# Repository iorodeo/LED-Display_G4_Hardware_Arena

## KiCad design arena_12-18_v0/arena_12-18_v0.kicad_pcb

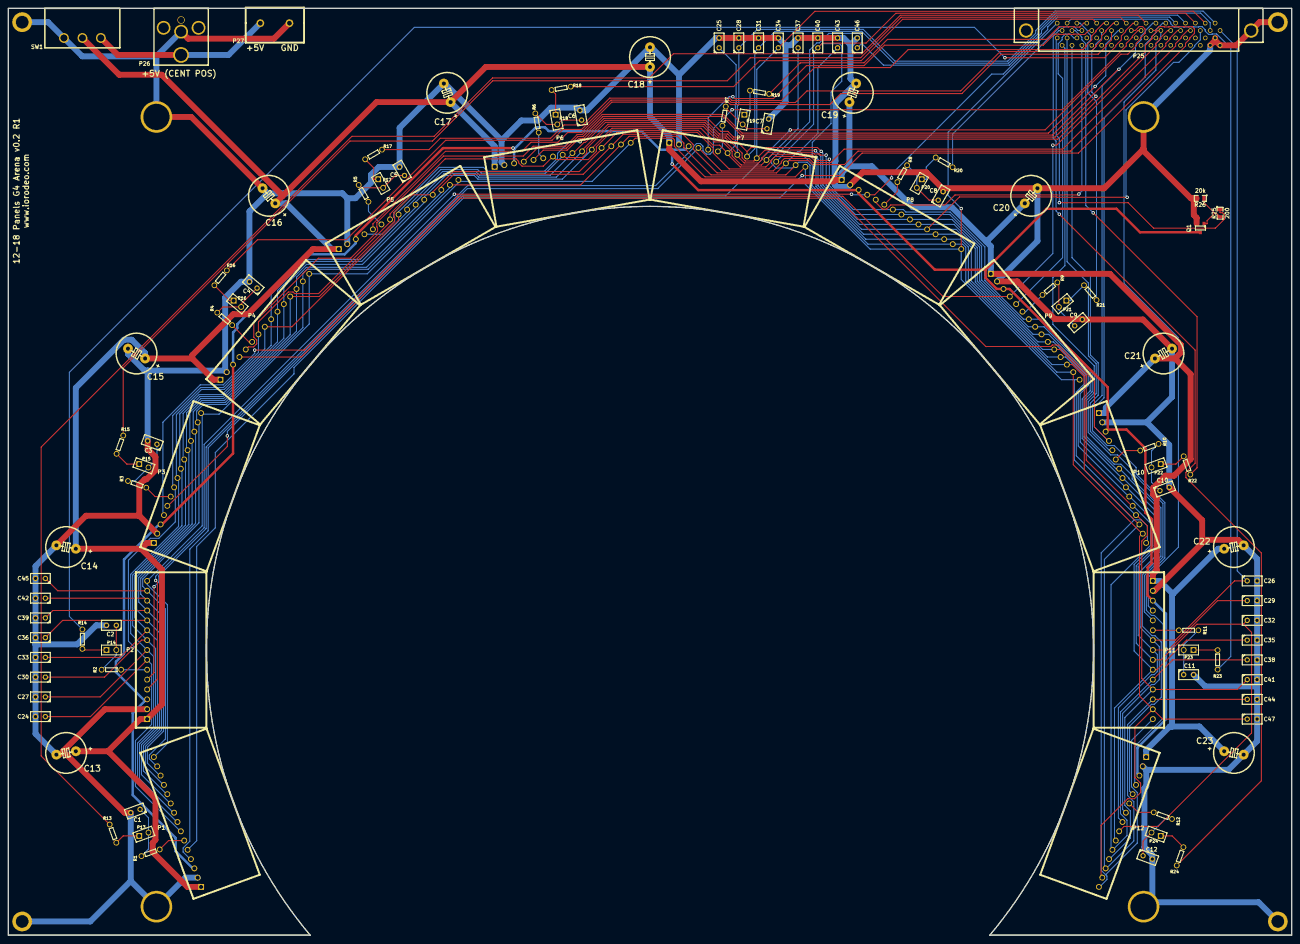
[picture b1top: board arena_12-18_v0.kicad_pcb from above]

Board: 2 copper layers, 330.2 x 238.5 mm, 110 parts (0 on the bottom side), 81 nets.

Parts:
C1, C2, C3, C4, C5, C6, C7, C8, C9, C10, C11, C12: C; C1
C13, C14, C15, C16, C17, C19, C20, C21, C22, C23: 10uF; Capacitor_Polarized
C18: 10uf; Capacitor_Polarized
C24, C25, C26, C27, C28, C29, C30, C31, C32, C33, C34, C35, C36, C37, C38, C39, C40, C41, C42, C43, C44, C45, C46, C47: 30pF; C1
P1, P2, P3, P4, P5, P6, P7, P8, P9, P10, P11, P12: CONN15; PANEL_G4
P13, P14, P15, P16, P17, P18, P19, P20, P21, P22, P23, P24: CONN_2; PIN_ARRAY_2X1
P25: CONN_34X2; TE_CONN_DSUB_RA_68
P26: CONN_2; DCJACK_2PIN_HIGHCURRENT
P27: CONN_2; TERM_7P5MM
P28, P29, P30, P31: CONN_1; 0P25_MOUNT_HOLE
P32, P33, P34, P35: CONN_1; #4_THROUGH_HOLE
Q1: MOSFET_NCHAN; SOT23
R1, R2, R3, R4, R5, R6, R7, R8, R9, R10, R11, R12, R13, R14, R15, R16, R17, R18, R19, R20, R21, R22, R23, R24: R; R_SMALL
R25: 200; SM0805
R26: 20k; SM0805
SW1: SWITCH_INV; slide_switch

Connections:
+5V: P26.1, P27.1, SW1.1
/5V: C13.1, C14.1, C15.1, C16.1, C17.1, C18.1, C19.1, C20.1, C21.1, C22.1, C23.1, P1.1, P2.1, P3.1, P4.1, P5.1, P6.1, P7.1, P8.1, P9.1, P10.1, P11.1, P12.1, SW1.2
/CS_0: C24.1, C25.1, C26.1, P1.7, P2.7, P3.7, P4.7, P5.7, P6.7, P7.7, P8.7, P9.7, P10.7, P11.7, P12.7, P25.35
/CS_1: C27.1, C28.1, C29.1, P1.8, P2.8, P3.8, P4.8, P5.8, P6.8, P7.8, P8.8, P9.8, P10.8, P11.8, P12.8, P25.36
/CS_2: C30.1, C31.1, C32.1, P1.9, P2.9, P3.9, P4.9, P5.9, P6.9, P7.9, P8.9, P9.9, P10.9, P11.9, P12.9, P25.37
/CS_3: C33.1, C34.1, C35.1, P1.10, P2.10, P3.10, P4.10, P5.10, P6.10, P7.10, P8.10, P9.10, P10.10, P11.10, P12.10, P25.38
/CS_4: C36.1, C37.1, C38.1, P1.11, P2.11, P3.11, P4.11, P5.11, P6.11, P7.11, P8.11, P9.11, P10.11, P11.11, P12.11, P25.39
/CS_5: C39.1, C40.1, C41.1, P1.12, P2.12, P3.12, P4.12, P5.12, P6.12, P7.12, P8.12, P9.12, P10.12, P11.12, P12.12, P25.40
/CS_6: C42.1, C43.1, C44.1, P1.13, P2.13, P3.13, P4.13, P5.13, P6.13, P7.13, P8.13, P9.13, P10.13, P11.13, P12.13, P25.41
/CS_7: C45.1, C46.1, C47.1, P1.14, P2.14, P3.14, P4.14, P5.14, P6.14, P7.14, P8.14, P9.14, P10.14, P11.14, P12.14, P25.42
/EXT_INT: P1.15, P2.15, P3.15, P4.15, P5.15, P6.15, P7.15, P8.15, P9.15, P10.15, P11.15, P12.15, P25.68
/MISO_0: P25.50, R13.2
/MISO_1: P25.52, R14.2
/MISO_2: P25.54, R15.2
/MISO_3: P25.56, R16.2
/MISO_4: P25.58, R17.2
/MISO_5: P25.60, R18.2
/MISO_6: P25.62, R19.2
/MISO_7: P25.63, R20.2
/MISO_8: P25.64, R21.2
/MISO_9: P25.65, R22.2
/MISO_10: P25.66, R23.2
/MISO_11: P25.67, R24.2
/MOSI_0: P1.5, P25.49
/MOSI_1: P2.5, P25.51
/MOSI_2: P3.5, P25.53
/MOSI_3: P4.5, P25.55
/MOSI_4: P5.5, P25.57
/MOSI_5: P6.5, P25.59
/MOSI_6: P7.5, P25.61
/MOSI_7: P8.5, P25.29
/MOSI_8: P9.5, P25.30
/MOSI_9: P10.5, P25.31
/MOSI_10: P11.5, P25.32
/MOSI_11: P12.5, P25.33
/RESET: P25.34, R25.1
/RESET_PAN: P1.3, P2.3, P3.3, P4.3, P5.3, P6.3, P7.3, P8.3, P9.3, P10.3, P11.3, P12.3, Q1.3
/SCK_0: P1.4, P7.4, P25.43
/SCK_1: P2.4, P8.4, P25.44
/SCK_2: P3.4, P9.4, P25.45
/SCK_3: P4.4, P10.4, P25.46
/SCK_4: P5.4, P11.4, P25.47
/SCK_5: P6.4, P12.4, P25.48
/_MISO_0: P1.6, R1.1
/_MISO_1: P2.6, R2.1
/_MISO_2: P3.6, R3.1
/_MISO_3: P4.6, R4.1
/_MISO_4: P5.6, R5.1
/_MISO_5: P6.6, R6.1
/_MISO_6: P7.6, R7.1
/_MISO_7: P8.6, R8.1
/_MISO_8: P9.6, R9.1
/_MISO_9: P10.6, R10.1
/_MISO_10: P11.6, R11.1
/_MISO_11: P12.6, R12.1
GND: C1.2, C2.2, C3.2, C4.2, C5.2, C6.2, C7.2, C8.2, C9.2, C10.2, C11.2, C12.2, C13.2, C14.2, C15.2, C16.2, C17.2, C18.2, C19.2, C20.2, C21.2, C22.2, C23.2, C24.2, C25.2, C26.2, C27.2, C28.2, C29.2, C30.2, C31.2, C32.2, C33.2, C34.2, C35.2, C36.2, C37.2, C38.2, C39.2, C40.2, C41.2, C42.2, C43.2, C44.2, C45.2, C46.2, C47.2, P1.2, P2.2, P3.2, P4.2, P5.2, P6.2, P7.2, P8.2, P9.2, P10.2, P11.2, P12.2, P25.1, P25.2, P25.3, P25.69, P26.2, P27.2, P28.1, P29.1, P30.1, P31.1, P32.1, P33.1, P34.1, P35.1, Q1.2, R26.2, SW1.3
unnamed: P24.1, R24.1
unnamed: P23.1, R23.1
unnamed: P20.1, R20.1
unnamed: P22.1, R22.1
unnamed: P21.1, R21.1
unnamed: P19.1, R19.1
unnamed: P18.1, R18.1
unnamed: P17.1, R17.1
unnamed: P16.1, R16.1
unnamed: P15.1, R15.1
unnamed: P14.1, R14.1
unnamed: P13.1, R13.1
unnamed: C4.1, P16.2, R4.2
unnamed: C3.1, P15.2, R3.2
unnamed: C2.1, P14.2, R2.2
unnamed: C1.1, P13.2, R1.2
unnamed: C5.1, P17.2, R5.2
unnamed: C12.1, P24.2, R12.2
unnamed: C7.1, P19.2, R7.2
unnamed: C6.1, P18.2, R6.2
unnamed: C9.1, P21.2, R9.2
unnamed: C8.1, P20.2, R8.2
unnamed: C11.1, P23.2, R11.2
unnamed: C10.1, P22.2, R10.2
unnamed: Q1.1, R25.2, R26.1

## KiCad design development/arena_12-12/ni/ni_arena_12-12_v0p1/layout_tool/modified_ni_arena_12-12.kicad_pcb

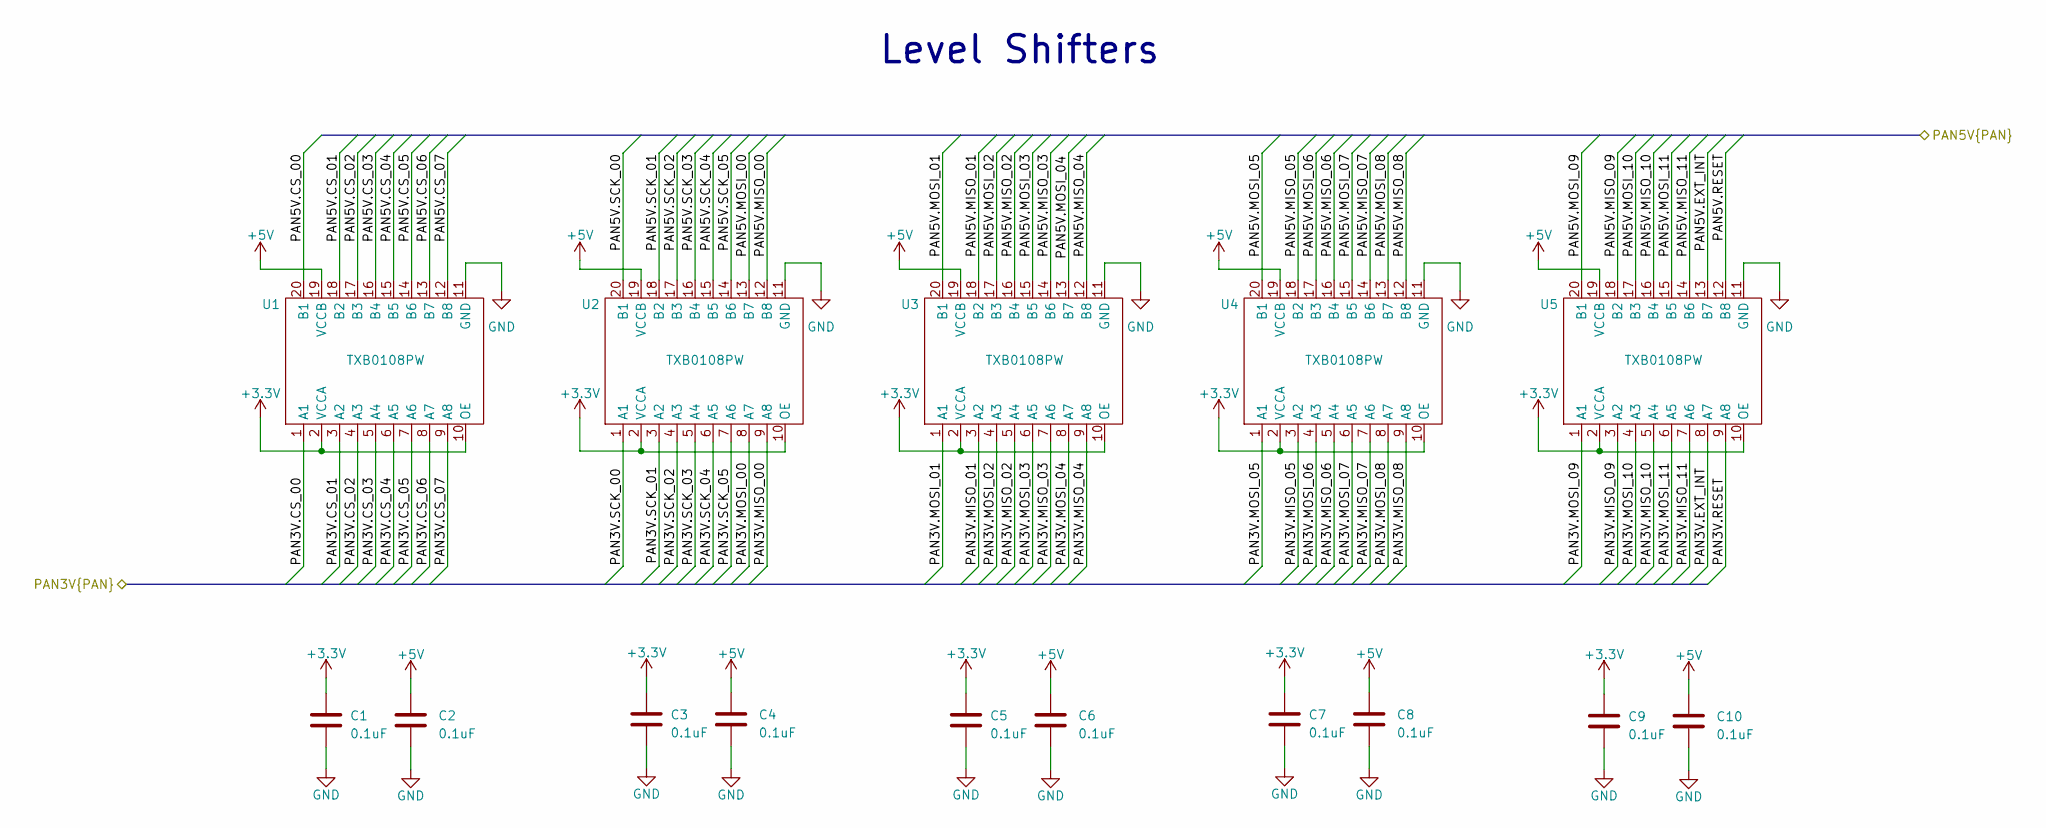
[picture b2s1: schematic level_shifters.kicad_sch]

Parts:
C1, C2, C3, C4, C5, C6, C7, C8, C9, C10: 0.1uF; C_0603_1608Metric
U1, U2, U3, U4, U5: TXB0108PW; TSSOP-20_4.4x6.5mm_P0.65mm

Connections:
+3.3V: C1.1, C3.1, C5.1, C7.1, C9.1, U1.2 (VCCA), U1.10 (OE), U2.2 (VCCA), U2.10 (OE), U3.2 (VCCA), U3.10 (OE), U4.2 (VCCA), U4.10 (OE), U5.2 (VCCA), U5.10 (OE); also elsewhere on the board
+5V: C2.1, C4.1, C6.1, C8.1, C10.1, U1.19 (VCCB), U2.19 (VCCB), U3.19 (VCCB), U4.19 (VCCB), U5.19 (VCCB); also elsewhere on the board
/Level Shifters/PAN3V.CS_00: U1.1 (A1); also elsewhere on the board
/Level Shifters/PAN3V.CS_01: U1.3 (A2); also elsewhere on the board
/Level Shifters/PAN3V.CS_02: U1.4 (A3); also elsewhere on the board
/Level Shifters/PAN3V.CS_03: U1.5 (A4); also elsewhere on the board
/Level Shifters/PAN3V.CS_04: U1.6 (A5); also elsewhere on the board
/Level Shifters/PAN3V.CS_05: U1.7 (A6); also elsewhere on the board
/Level Shifters/PAN3V.CS_06: U1.8 (A7); also elsewhere on the board
/Level Shifters/PAN3V.CS_07: U1.9 (A8); also elsewhere on the board
/Level Shifters/PAN3V.EXT_INT: U5.8 (A7); also elsewhere on the board
/Level Shifters/PAN3V.MISO_00: U2.9 (A8); also elsewhere on the board
/Level Shifters/PAN3V.MISO_01: U3.3 (A2); also elsewhere on the board
/Level Shifters/PAN3V.MISO_02: U3.5 (A4); also elsewhere on the board
/Level Shifters/PAN3V.MISO_03: U3.7 (A6); also elsewhere on the board
/Level Shifters/PAN3V.MISO_04: U3.9 (A8); also elsewhere on the board
/Level Shifters/PAN3V.MISO_05: U4.3 (A2); also elsewhere on the board
/Level Shifters/PAN3V.MISO_06: U4.5 (A4); also elsewhere on the board
/Level Shifters/PAN3V.MISO_07: U4.7 (A6); also elsewhere on the board
/Level Shifters/PAN3V.MISO_08: U4.9 (A8); also elsewhere on the board
/Level Shifters/PAN3V.MISO_09: U5.3 (A2); also elsewhere on the board
/Level Shifters/PAN3V.MISO_10: U5.5 (A4); also elsewhere on the board
/Level Shifters/PAN3V.MISO_11: U5.7 (A6); also elsewhere on the board
/Level Shifters/PAN3V.MOSI_00: U2.8 (A7); also elsewhere on the board
/Level Shifters/PAN3V.MOSI_01: U3.1 (A1); also elsewhere on the board
/Level Shifters/PAN3V.MOSI_02: U3.4 (A3); also elsewhere on the board
/Level Shifters/PAN3V.MOSI_03: U3.6 (A5); also elsewhere on the board
/Level Shifters/PAN3V.MOSI_04: U3.8 (A7); also elsewhere on the board
/Level Shifters/PAN3V.MOSI_05: U4.1 (A1); also elsewhere on the board
/Level Shifters/PAN3V.MOSI_06: U4.4 (A3); also elsewhere on the board
/Level Shifters/PAN3V.MOSI_07: U4.6 (A5); also elsewhere on the board
/Level Shifters/PAN3V.MOSI_08: U4.8 (A7); also elsewhere on the board
/Level Shifters/PAN3V.MOSI_09: U5.1 (A1); also elsewhere on the board
/Level Shifters/PAN3V.MOSI_10: U5.4 (A3); also elsewhere on the board
/Level Shifters/PAN3V.MOSI_11: U5.6 (A5); also elsewhere on the board
/Level Shifters/PAN3V.RESET: U5.9 (A8); also elsewhere on the board
/Level Shifters/PAN3V.SCK_00: U2.1 (A1); also elsewhere on the board
/Level Shifters/PAN3V.SCK_01: U2.3 (A2); also elsewhere on the board
/Level Shifters/PAN3V.SCK_02: U2.4 (A3); also elsewhere on the board
/Level Shifters/PAN3V.SCK_03: U2.5 (A4); also elsewhere on the board
/Level Shifters/PAN3V.SCK_04: U2.6 (A5); also elsewhere on the board
/Level Shifters/PAN3V.SCK_05: U2.7 (A6); also elsewhere on the board
/Level Shifters/PAN5V.CS_00: U1.20 (B1); also elsewhere on the board
/Level Shifters/PAN5V.CS_01: U1.18 (B2); also elsewhere on the board
/Level Shifters/PAN5V.CS_02: U1.17 (B3); also elsewhere on the board
/Level Shifters/PAN5V.CS_03: U1.16 (B4); also elsewhere on the board
/Level Shifters/PAN5V.CS_04: U1.15 (B5); also elsewhere on the board
/Level Shifters/PAN5V.CS_05: U1.14 (B6); also elsewhere on the board
/Level Shifters/PAN5V.CS_06: U1.13 (B7); also elsewhere on the board
/Level Shifters/PAN5V.CS_07: U1.12 (B8); also elsewhere on the board
/Level Shifters/PAN5V.EXT_INT: U5.13 (B7); also elsewhere on the board
/Level Shifters/PAN5V.MISO_00: U2.12 (B8); also elsewhere on the board
/Level Shifters/PAN5V.MISO_01: U3.18 (B2); also elsewhere on the board
/Level Shifters/PAN5V.MISO_02: U3.16 (B4); also elsewhere on the board
/Level Shifters/PAN5V.MISO_03: U3.14 (B6); also elsewhere on the board
/Level Shifters/PAN5V.MISO_04: U3.12 (B8); also elsewhere on the board
/Level Shifters/PAN5V.MISO_05: U4.18 (B2); also elsewhere on the board
/Level Shifters/PAN5V.MISO_06: U4.16 (B4); also elsewhere on the board
/Level Shifters/PAN5V.MISO_07: U4.14 (B6); also elsewhere on the board
/Level Shifters/PAN5V.MISO_08: U4.12 (B8); also elsewhere on the board
/Level Shifters/PAN5V.MISO_09: U5.18 (B2); also elsewhere on the board
/Level Shifters/PAN5V.MISO_10: U5.16 (B4); also elsewhere on the board
/Level Shifters/PAN5V.MISO_11: U5.14 (B6); also elsewhere on the board
/Level Shifters/PAN5V.MOSI_00: U2.13 (B7); also elsewhere on the board
/Level Shifters/PAN5V.MOSI_01: U3.20 (B1); also elsewhere on the board
/Level Shifters/PAN5V.MOSI_02: U3.17 (B3); also elsewhere on the board
/Level Shifters/PAN5V.MOSI_03: U3.15 (B5); also elsewhere on the board
/Level Shifters/PAN5V.MOSI_04: U3.13 (B7); also elsewhere on the board
/Level Shifters/PAN5V.MOSI_05: U4.20 (B1); also elsewhere on the board
/Level Shifters/PAN5V.MOSI_06: U4.17 (B3); also elsewhere on the board
/Level Shifters/PAN5V.MOSI_07: U4.15 (B5); also elsewhere on the board
/Level Shifters/PAN5V.MOSI_08: U4.13 (B7); also elsewhere on the board
/Level Shifters/PAN5V.MOSI_09: U5.20 (B1); also elsewhere on the board
/Level Shifters/PAN5V.MOSI_10: U5.17 (B3); also elsewhere on the board
/Level Shifters/PAN5V.MOSI_11: U5.15 (B5); also elsewhere on the board
/Level Shifters/PAN5V.RESET: U5.12 (B8); also elsewhere on the board
/Level Shifters/PAN5V.SCK_00: U2.20 (B1); also elsewhere on the board
/Level Shifters/PAN5V.SCK_01: U2.18 (B2); also elsewhere on the board
/Level Shifters/PAN5V.SCK_02: U2.17 (B3); also elsewhere on the board
/Level Shifters/PAN5V.SCK_03: U2.16 (B4); also elsewhere on the board
/Level Shifters/PAN5V.SCK_04: U2.15 (B5); also elsewhere on the board
/Level Shifters/PAN5V.SCK_05: U2.14 (B6); also elsewhere on the board
GND: C1.2, C2.2, C3.2, C4.2, C5.2, C6.2, C7.2, C8.2, C9.2, C10.2, U1.11 (GND), U2.11 (GND), U3.11 (GND), U4.11 (GND), U5.11 (GND); also elsewhere on the board

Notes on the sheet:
Level Shifters

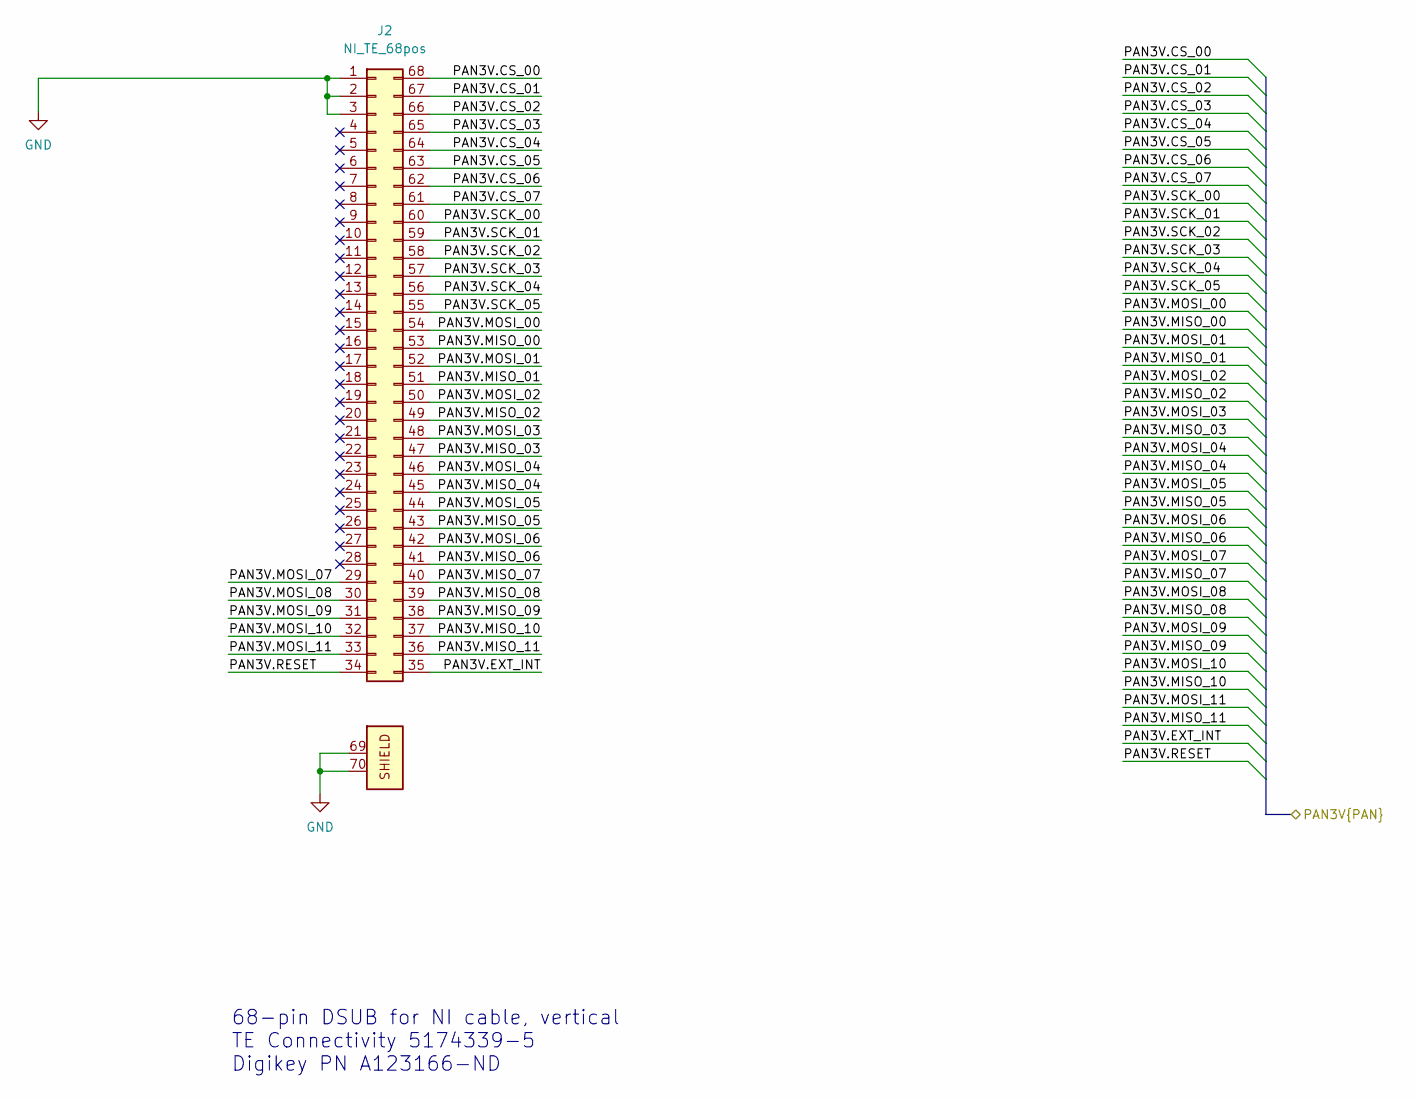
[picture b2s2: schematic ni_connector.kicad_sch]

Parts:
J2: NI_TE_68pos; TE_CONN_DSUB_VERT_68

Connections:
/Level Shifters/PAN3V.CS_00: J2.68; also elsewhere on the board
/Level Shifters/PAN3V.CS_01: J2.67; also elsewhere on the board
/Level Shifters/PAN3V.CS_02: J2.66; also elsewhere on the board
/Level Shifters/PAN3V.CS_03: J2.65; also elsewhere on the board
/Level Shifters/PAN3V.CS_04: J2.64; also elsewhere on the board
/Level Shifters/PAN3V.CS_05: J2.63; also elsewhere on the board
/Level Shifters/PAN3V.CS_06: J2.62; also elsewhere on the board
/Level Shifters/PAN3V.CS_07: J2.61; also elsewhere on the board
/Level Shifters/PAN3V.EXT_INT: J2.35; also elsewhere on the board
/Level Shifters/PAN3V.MISO_00: J2.53; also elsewhere on the board
/Level Shifters/PAN3V.MISO_01: J2.51; also elsewhere on the board
/Level Shifters/PAN3V.MISO_02: J2.49; also elsewhere on the board
/Level Shifters/PAN3V.MISO_03: J2.47; also elsewhere on the board
/Level Shifters/PAN3V.MISO_04: J2.45; also elsewhere on the board
/Level Shifters/PAN3V.MISO_05: J2.43; also elsewhere on the board
/Level Shifters/PAN3V.MISO_06: J2.41; also elsewhere on the board
/Level Shifters/PAN3V.MISO_07: J2.40; also elsewhere on the board
/Level Shifters/PAN3V.MISO_08: J2.39; also elsewhere on the board
/Level Shifters/PAN3V.MISO_09: J2.38; also elsewhere on the board
/Level Shifters/PAN3V.MISO_10: J2.37; also elsewhere on the board
/Level Shifters/PAN3V.MISO_11: J2.36; also elsewhere on the board
/Level Shifters/PAN3V.MOSI_00: J2.54; also elsewhere on the board
/Level Shifters/PAN3V.MOSI_01: J2.52; also elsewhere on the board
/Level Shifters/PAN3V.MOSI_02: J2.50; also elsewhere on the board
/Level Shifters/PAN3V.MOSI_03: J2.48; also elsewhere on the board
/Level Shifters/PAN3V.MOSI_04: J2.46; also elsewhere on the board
/Level Shifters/PAN3V.MOSI_05: J2.44; also elsewhere on the board
/Level Shifters/PAN3V.MOSI_06: J2.42; also elsewhere on the board
/Level Shifters/PAN3V.MOSI_07: J2.29; also elsewhere on the board
/Level Shifters/PAN3V.MOSI_08: J2.30; also elsewhere on the board
/Level Shifters/PAN3V.MOSI_09: J2.31; also elsewhere on the board
/Level Shifters/PAN3V.MOSI_10: J2.32; also elsewhere on the board
/Level Shifters/PAN3V.MOSI_11: J2.33; also elsewhere on the board
/Level Shifters/PAN3V.RESET: J2.34; also elsewhere on the board
/Level Shifters/PAN3V.SCK_00: J2.60; also elsewhere on the board
/Level Shifters/PAN3V.SCK_01: J2.59; also elsewhere on the board
/Level Shifters/PAN3V.SCK_02: J2.58; also elsewhere on the board
/Level Shifters/PAN3V.SCK_03: J2.57; also elsewhere on the board
/Level Shifters/PAN3V.SCK_04: J2.56; also elsewhere on the board
/Level Shifters/PAN3V.SCK_05: J2.55; also elsewhere on the board
GND: J2.1, J2.2, J2.3, J2.69 (GND), J2.70 (GND); also elsewhere on the board

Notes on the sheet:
68-pin DSUB for NI cable, vertical TE Connectivity 5174339-5 Digikey PN A123166-ND

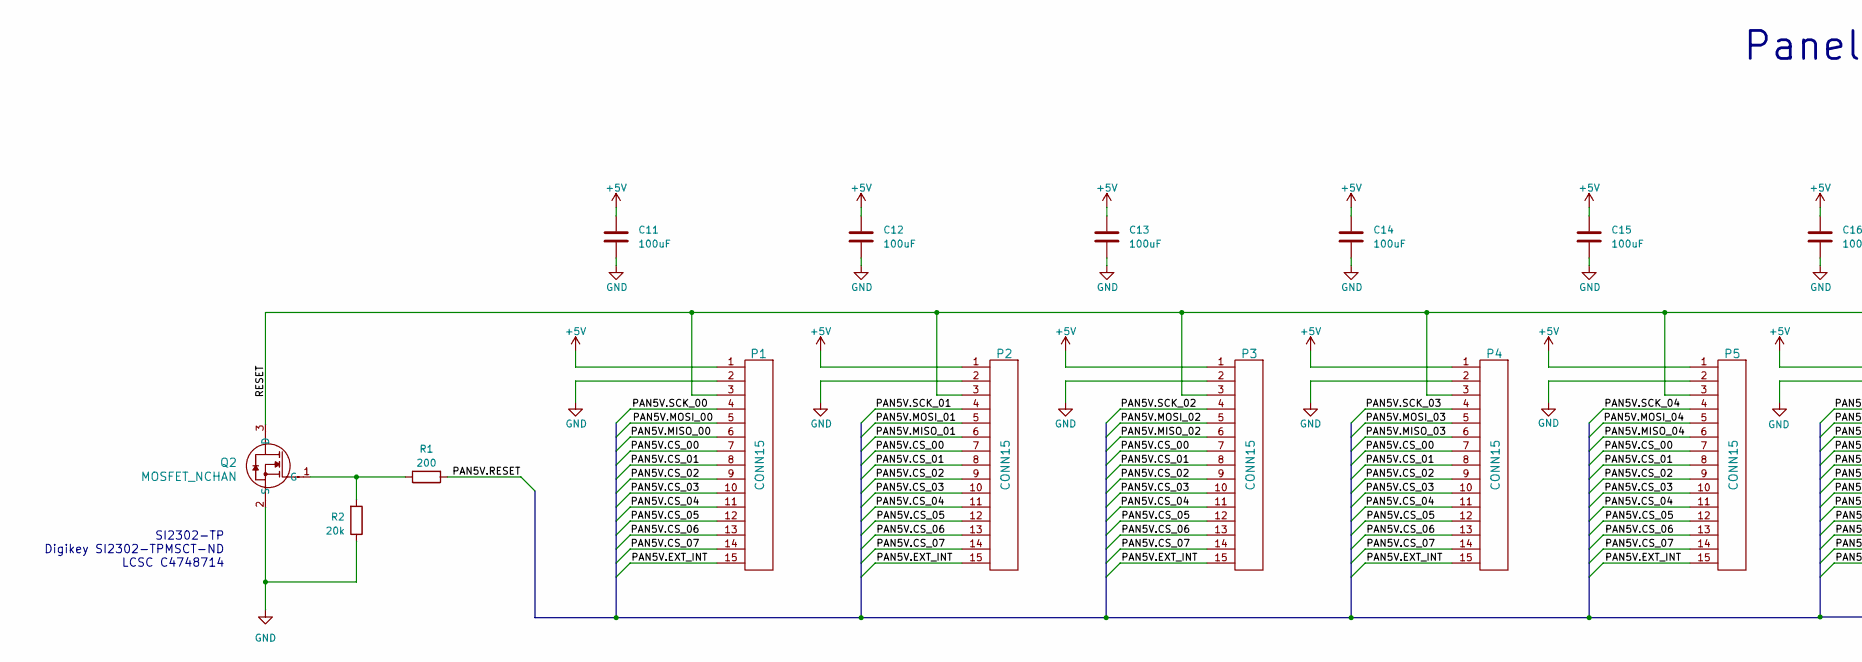
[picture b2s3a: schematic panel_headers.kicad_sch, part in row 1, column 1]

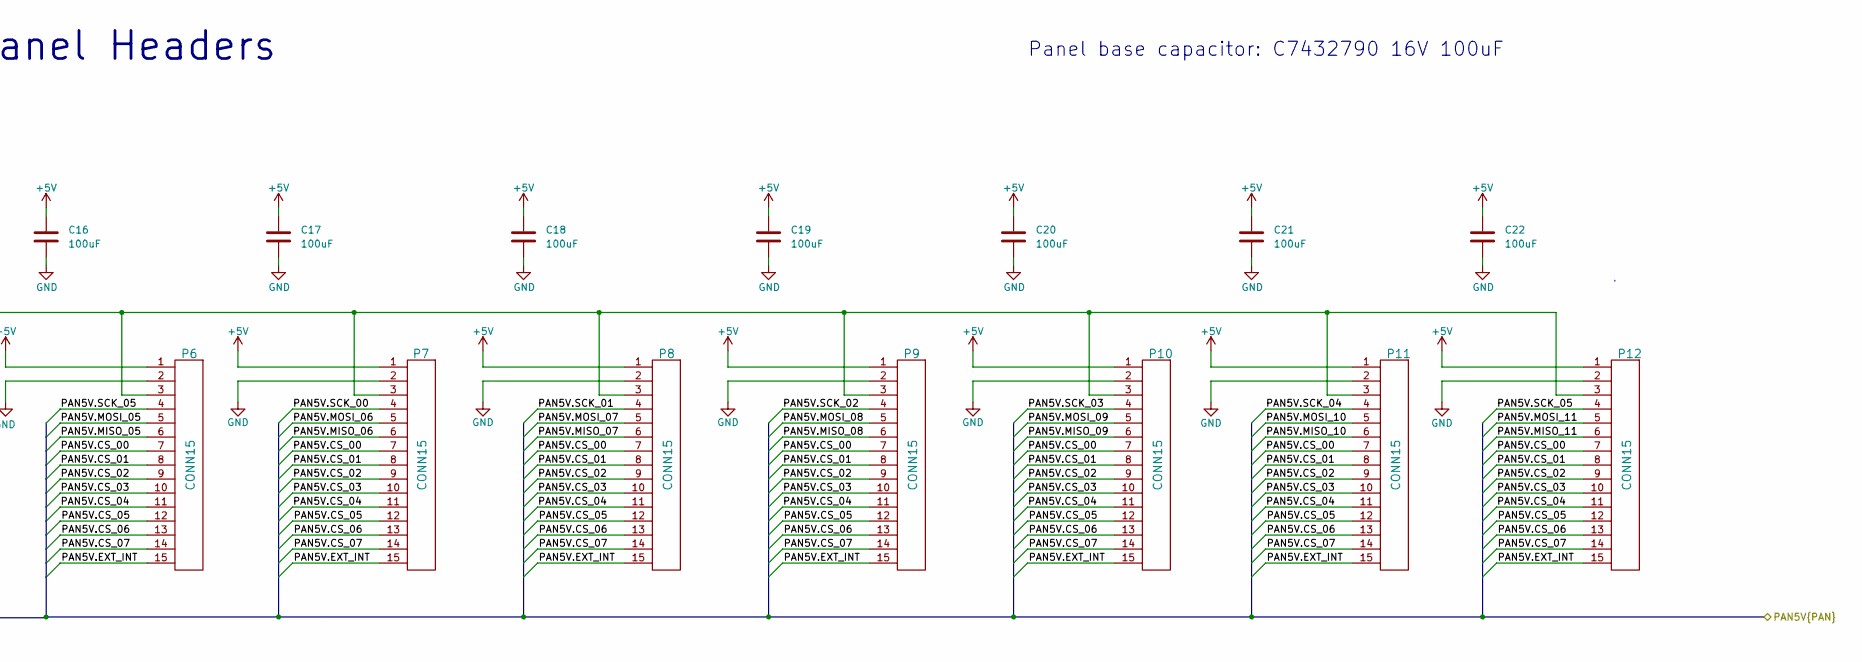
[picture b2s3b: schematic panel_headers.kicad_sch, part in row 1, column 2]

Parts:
C11, C12, C13, C14, C15, C16, C17, C18, C19, C20, C21, C22: 100uF; C_1210_3225Metric
P1, P2, P3, P4, P5, P6, P7, P8, P9, P10, P11, P12: CONN15; HEADER_TOP
Q2: MOSFET_NCHAN; SOT-23-3
R1: 200; R_0805_2012Metric
R2: 20k; R_0805_2012Metric

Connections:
+5V: C11.1, C12.1, C13.1, C14.1, C15.1, C16.1, C17.1, C18.1, C19.1, C20.1, C21.1, C22.1, P1.1, P2.1, P3.1, P4.1, P5.1, P6.1, P7.1, P8.1, P9.1, P10.1, P11.1, P12.1; also elsewhere on the board
/Level Shifters/PAN5V.CS_00: P1.7, P2.7, P3.7, P4.7, P5.7, P6.7, P7.7, P8.7, P9.7, P10.7, P11.7, P12.7; also elsewhere on the board
/Level Shifters/PAN5V.CS_01: P1.8, P2.8, P3.8, P4.8, P5.8, P6.8, P7.8, P8.8, P9.8, P10.8, P11.8, P12.8; also elsewhere on the board
/Level Shifters/PAN5V.CS_02: P1.9, P2.9, P3.9, P4.9, P5.9, P6.9, P7.9, P8.9, P9.9, P10.9, P11.9, P12.9; also elsewhere on the board
/Level Shifters/PAN5V.CS_03: P1.10, P2.10, P3.10, P4.10, P5.10, P6.10, P7.10, P8.10, P9.10, P10.10, P11.10, P12.10; also elsewhere on the board
/Level Shifters/PAN5V.CS_04: P1.11, P2.11, P3.11, P4.11, P5.11, P6.11, P7.11, P8.11, P9.11, P10.11, P11.11, P12.11; also elsewhere on the board
/Level Shifters/PAN5V.CS_05: P1.12, P2.12, P3.12, P4.12, P5.12, P6.12, P7.12, P8.12, P9.12, P10.12, P11.12, P12.12; also elsewhere on the board
/Level Shifters/PAN5V.CS_06: P1.13, P2.13, P3.13, P4.13, P5.13, P6.13, P7.13, P8.13, P9.13, P10.13, P11.13, P12.13; also elsewhere on the board
/Level Shifters/PAN5V.CS_07: P1.14, P2.14, P3.14, P4.14, P5.14, P6.14, P7.14, P8.14, P9.14, P10.14, P11.14, P12.14; also elsewhere on the board
/Level Shifters/PAN5V.EXT_INT: P1.15, P2.15, P3.15, P4.15, P5.15, P6.15, P7.15, P8.15, P9.15, P10.15, P11.15, P12.15; also elsewhere on the board
/Level Shifters/PAN5V.MISO_00: P1.6; also elsewhere on the board
/Level Shifters/PAN5V.MISO_01: P2.6; also elsewhere on the board
/Level Shifters/PAN5V.MISO_02: P3.6; also elsewhere on the board
/Level Shifters/PAN5V.MISO_03: P4.6; also elsewhere on the board
/Level Shifters/PAN5V.MISO_04: P5.6; also elsewhere on the board
/Level Shifters/PAN5V.MISO_05: P6.6; also elsewhere on the board
/Level Shifters/PAN5V.MISO_06: P7.6; also elsewhere on the board
/Level Shifters/PAN5V.MISO_07: P8.6; also elsewhere on the board
/Level Shifters/PAN5V.MISO_08: P9.6; also elsewhere on the board
/Level Shifters/PAN5V.MISO_09: P10.6; also elsewhere on the board
/Level Shifters/PAN5V.MISO_10: P11.6; also elsewhere on the board
/Level Shifters/PAN5V.MISO_11: P12.6; also elsewhere on the board
/Level Shifters/PAN5V.MOSI_00: P1.5; also elsewhere on the board
/Level Shifters/PAN5V.MOSI_01: P2.5; also elsewhere on the board
/Level Shifters/PAN5V.MOSI_02: P3.5; also elsewhere on the board
/Level Shifters/PAN5V.MOSI_03: P4.5; also elsewhere on the board
/Level Shifters/PAN5V.MOSI_04: P5.5; also elsewhere on the board
/Level Shifters/PAN5V.MOSI_05: P6.5; also elsewhere on the board
/Level Shifters/PAN5V.MOSI_06: P7.5; also elsewhere on the board
/Level Shifters/PAN5V.MOSI_07: P8.5; also elsewhere on the board
/Level Shifters/PAN5V.MOSI_08: P9.5; also elsewhere on the board
/Level Shifters/PAN5V.MOSI_09: P10.5; also elsewhere on the board
/Level Shifters/PAN5V.MOSI_10: P11.5; also elsewhere on the board
/Level Shifters/PAN5V.MOSI_11: P12.5; also elsewhere on the board
/Level Shifters/PAN5V.RESET: R1.2; also elsewhere on the board
/Level Shifters/PAN5V.SCK_00: P1.4, P7.4; also elsewhere on the board
/Level Shifters/PAN5V.SCK_01: P2.4, P8.4; also elsewhere on the board
/Level Shifters/PAN5V.SCK_02: P3.4, P9.4; also elsewhere on the board
/Level Shifters/PAN5V.SCK_03: P4.4, P10.4; also elsewhere on the board
/Level Shifters/PAN5V.SCK_04: P5.4, P11.4; also elsewhere on the board
/Level Shifters/PAN5V.SCK_05: P6.4, P12.4; also elsewhere on the board
/Panel Headers/RESET: P1.3, P2.3, P3.3, P4.3, P5.3, P6.3, P7.3, P8.3, P9.3, P10.3, P11.3, P12.3, Q2.3 (D)
GND: C11.2, C12.2, C13.2, C14.2, C15.2, C16.2, C17.2, C18.2, C19.2, C20.2, C21.2, C22.2, P1.2, P2.2, P3.2, P4.2, P5.2, P6.2, P7.2, P8.2, P9.2, P10.2, P11.2, P12.2, Q2.2 (S), R2.1; also elsewhere on the board
unnamed: Q2.1 (G), R1.1, R2.2

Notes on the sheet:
Panel base capacitor: C7432790 16V 100uF
Panel Headers
SI2302-TP Digikey SI2302-TPMSCT-ND LCSC C4748714

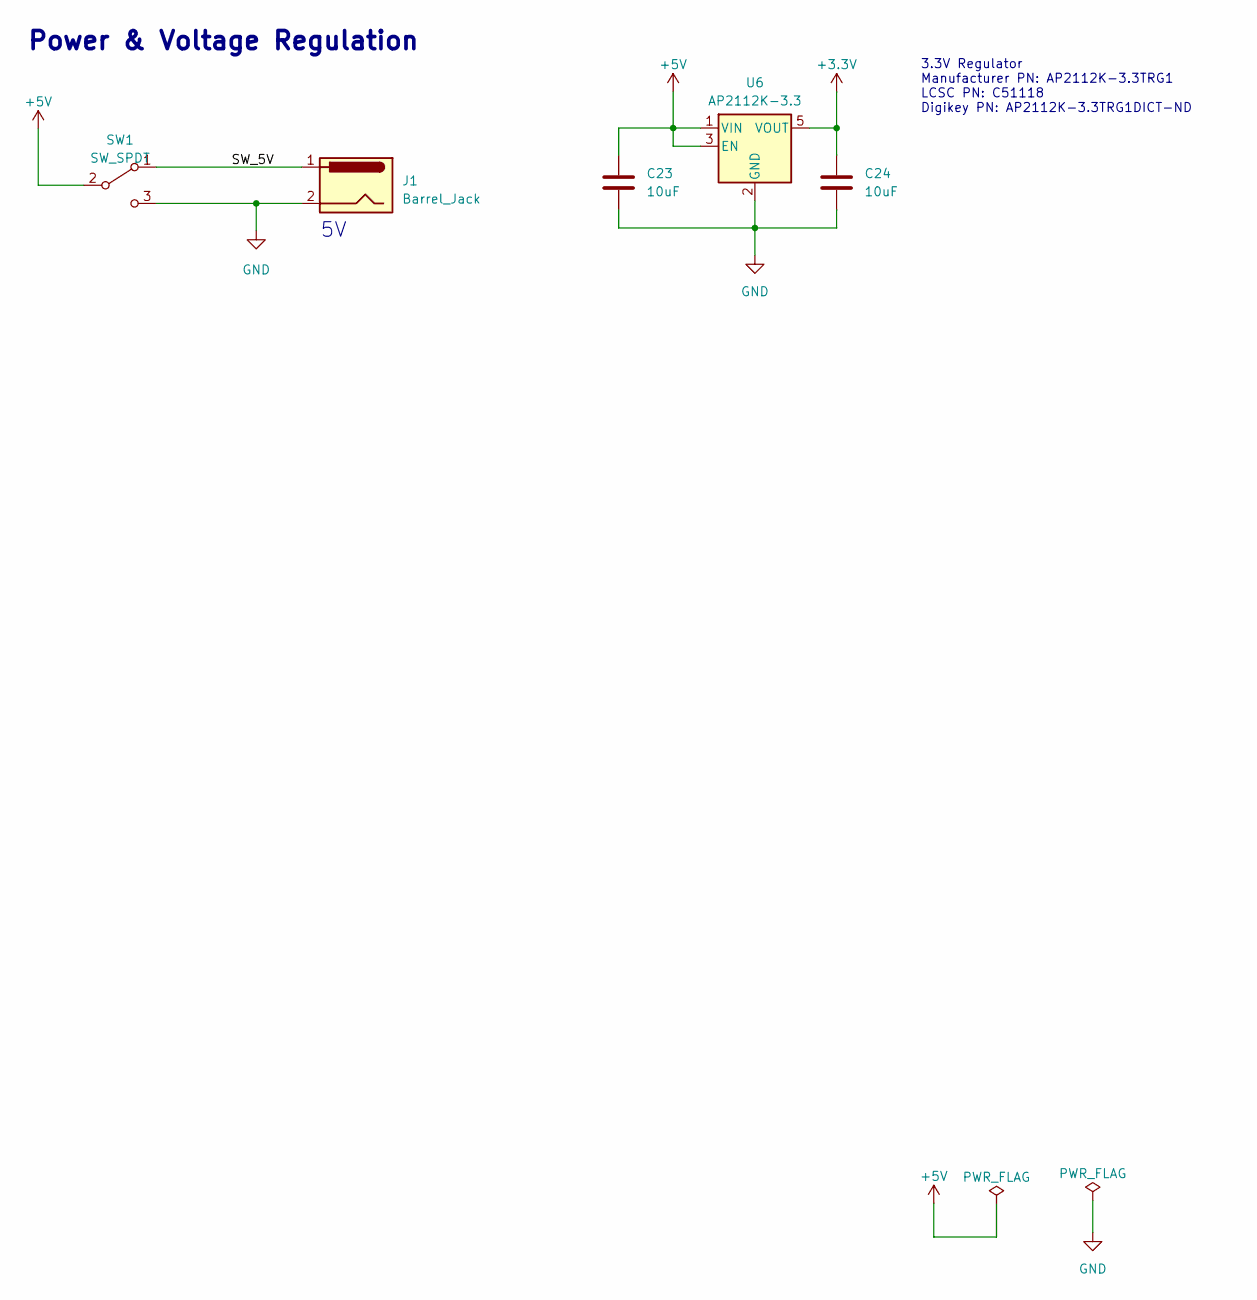
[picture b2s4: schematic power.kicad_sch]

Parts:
C23, C24: 10uF; C_0603_1608Metric
J1: Barrel_Jack; DCJACK_2PIN_HIGHCURRENT
SW1: SW_SPDT; slide_switch
U6: AP2112K-3.3; SOT-23-5

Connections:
+3.3V: C24.1, U6.5 (VOUT); also elsewhere on the board
+5V: C23.1, SW1.2 (B), U6.1 (VIN), U6.3 (EN); also elsewhere on the board
GND: C23.2, C24.2, J1.2, SW1.3 (C), U6.2 (GND); also elsewhere on the board
unnamed: J1.1, SW1.1 (A)

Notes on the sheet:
3.3V Regulator Manufacturer PN: AP2112K-3.3TRG1 LCSC PN: C51118 Digikey PN: AP2112K-3.3TRG1DICT-ND
Power & Voltage Regulation

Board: 4 copper layers, 54 parts (0 on the bottom side), 86 nets, no tracks yet.

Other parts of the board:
H1, H2, H3, H4, H5, H6: MountingHole_Pad; MountingHole_4.5mm_Pad

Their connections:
GND: H1.1, H2.1, H3.1, H4.1, H5.1, H6.1; also elsewhere on the board
